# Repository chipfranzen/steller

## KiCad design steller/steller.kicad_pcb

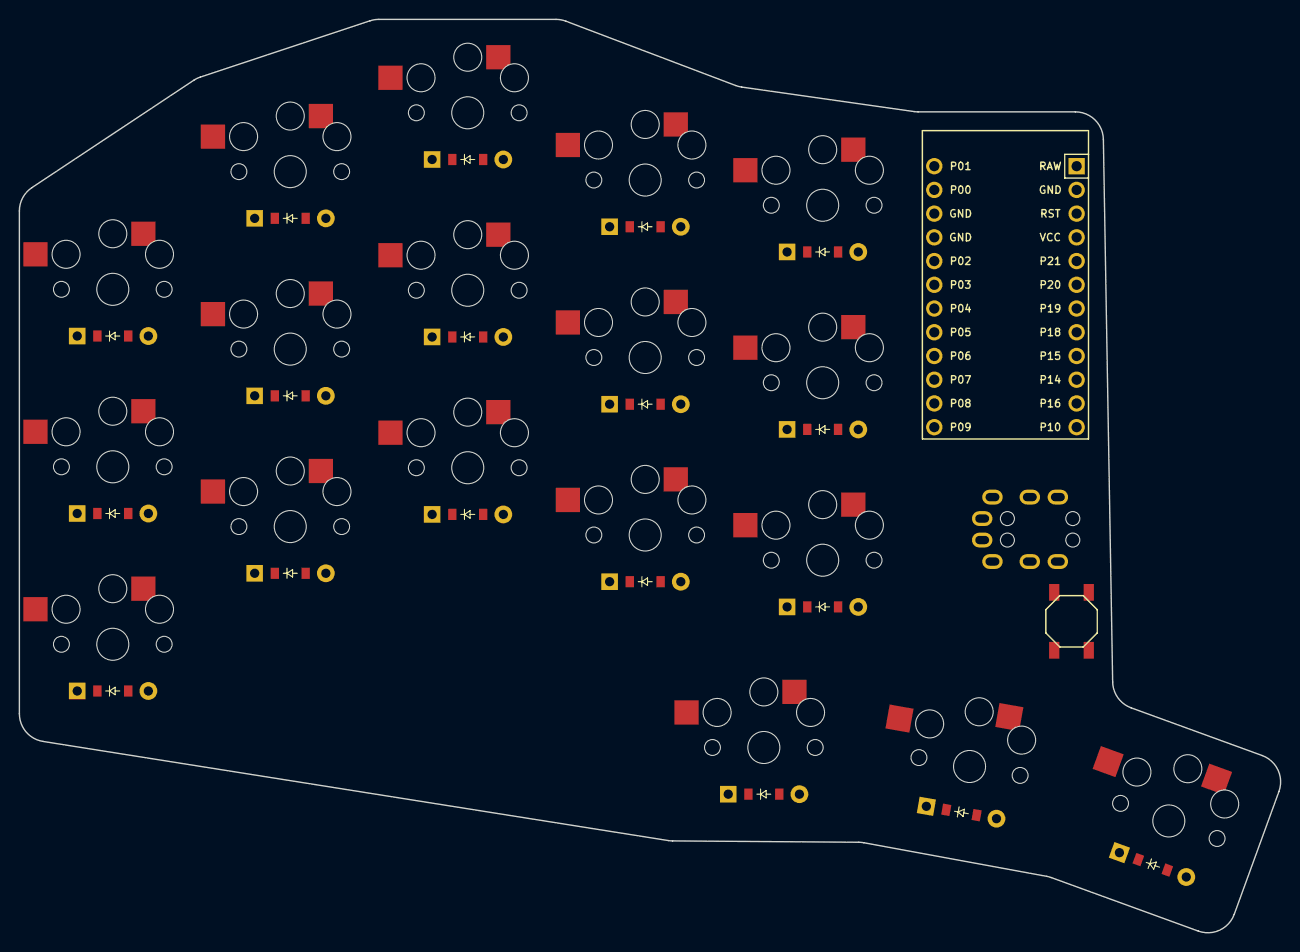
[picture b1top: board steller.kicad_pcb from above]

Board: 2 copper layers, 135.0 x 97.8 mm, 39 parts (0 on the bottom side), 22 nets, no tracks yet.

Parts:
B1: SW_TACT_ALPS_SKQGABE010
D1, D2, D3, D4, D5, D6, D7, D8, D9, D10, D11, D12, D13, D14, D15, D16, D17, D18: ComboDiode
MCU1: ProMicro
S1, S2, S3, S4, S5, S6, S7, S8, S9, S10, S11, S12, S13, S14, S15, S16, S17, S18: PG1350
TRRS1: trrs_pj320a (reversible)

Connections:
GND: B1.1, MCU1.2, MCU1.15, MCU1.16, TRRS1.2, TRRS1.4
P1: MCU1.13, TRRS1.3
RST: B1.2, MCU1.3
VCC: MCU1.4, TRRS1.5
home_cluster: D16.2, S16.2
index_bottom: D10.2, S10.2
index_home: D11.2, S11.2
index_top: D12.2, S12.2
inner_bottom: D13.2, S13.2
inner_cluster: D17.2, S17.2
inner_home: D14.2, S14.2
inner_top: D15.2, S15.2
middle_bottom: D7.2, S7.2
middle_home: D8.2, S8.2
middle_top: D9.2, S9.2
outer_cluster: D18.2, S18.2
pinky_bottom: D1.2, S1.2
pinky_home: D2.2, S2.2
pinky_top: D3.2, S3.2
ring_bottom: D4.2, S4.2
ring_home: D5.2, S5.2
ring_top: D6.2, S6.2

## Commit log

2025-07-04 Create index.norg.
2025-07-04 Add info to index.norg.
2025-07-04 Update index.norg even more.
    - Add design decisions.
2025-07-04 Add TODOS.
2025-07-06 Ergogen layout.
2025-07-11 Board outline.
2025-07-11 Key matrix.
2025-07-15 Pcb.
    Initial pcb.
2025-07-15 trrs, reset button.
2025-07-28 Pinky rework.
2025-07-31 Component positioning.
    Microprocessor
    trrs
    button
2025-07-31 Create logo.
2025-07-31 Update index.norg.
2025-08-03 Update logo.
